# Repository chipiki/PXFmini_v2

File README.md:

# PXFmini_v2
It's attempt to make a second version of died project PXFmini

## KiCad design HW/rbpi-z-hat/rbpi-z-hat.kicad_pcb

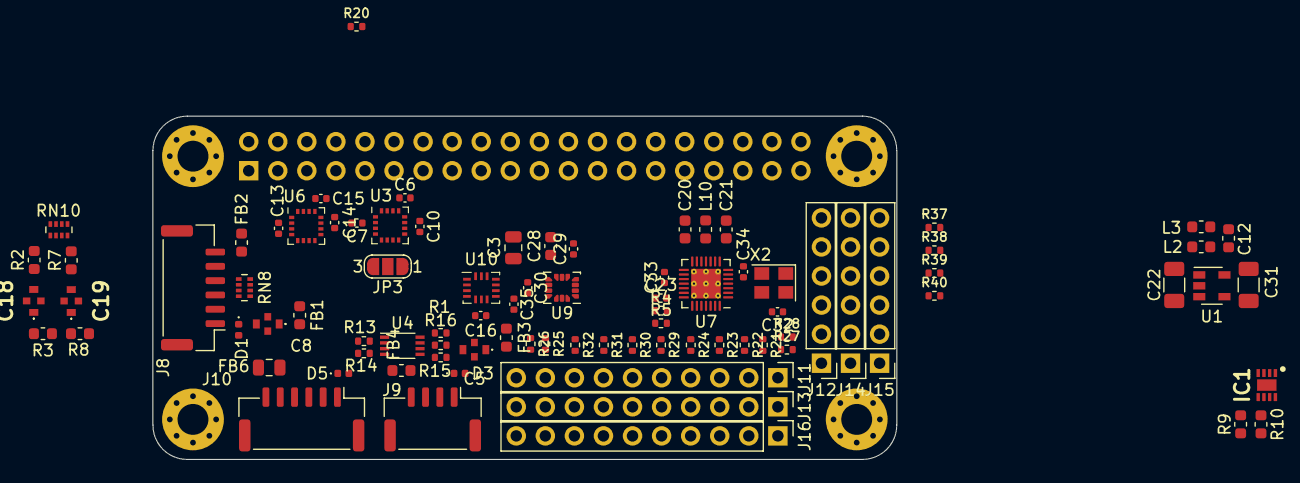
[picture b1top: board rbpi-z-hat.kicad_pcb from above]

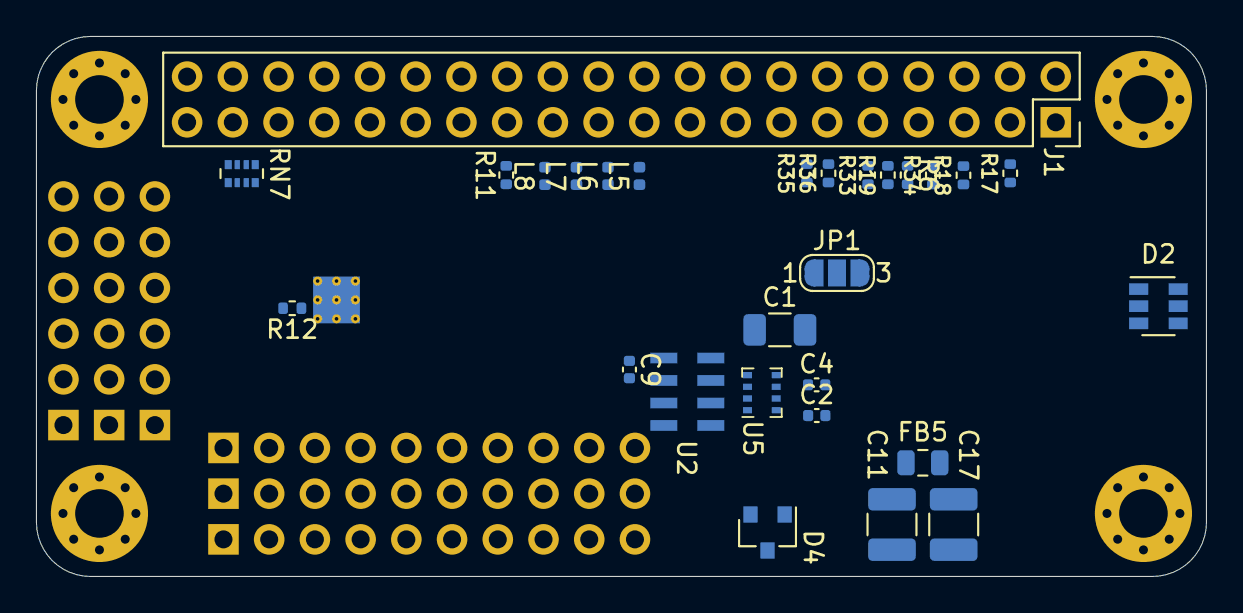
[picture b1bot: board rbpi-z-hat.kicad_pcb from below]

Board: 4 copper layers, 65.0 x 30.0 mm, 119 parts (28 on the bottom side), 92 nets, no tracks yet.

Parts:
C1, C22, C31: 22uF/10V; C_1206_3216Metric
C2, C4, C9: 100nF; C_0402_1005Metric
C3: 22uF/10V; C_0805_2012Metric
C5, C8: 1uF/16V/0805/NFM21PC105B1C3D; NFM21PC105B1C3D
C6, C7, C13, C15, C16, C23, C30, C32, C33, C34, C35: 0.1uF; C_0402_1005Metric
C10, C14: 4.7uF; C_0402_1005Metric
C11, C17: 22uF/16V; C_1210_3225Metric
C12: 100nF; C_0603_1608Metric
C18, C19: 1uF/16V/NFM21PC105B1C3D; NFM21PC105B1C3D
C20, C21: 10uF; C_0603_1608Metric
C28: 4.7uF; C_0603_1608Metric
C29: 10nF; C_0402_1005Metric
D1, D3, D5: PESD0402-140; D_0402_1005Metric
D2: ESDA5V3SC5; SOT-23-6
D4: PESD3V3S2UT; SOT-23
FB1, FB2, FB3, FB4: Ferrite_Bead; L_0603_1608Metric
FB5, FB6: MPZ2012S221AT000; L_0805_2012Metric
IC1: BQ24315DSGR; SON50P200X200X80-9N
J1: RBPI_CONN; PinSocket_2x20_P2.54mm_Vertical
J8: Conn_01x06_MountingPin; JST_GH_BM06B-GHS-TBT_1x06-1MP_P1.25mm_Vertical
J9: JST_GH; JST_GH_BM04B-GHS-TBT_1x04-1MP_P1.25mm_Vertical
J10: JST_GH; JST_GH_BM06B-GHS-TBT_1x06-1MP_P1.25mm_Vertical
J11, J13, J16: Conn_01x10; PinHeader_1x10_P2.54mm_Vertical
J12, J14, J15: Conn_01x06; PinHeader_1x06_P2.54mm_Vertical
JP1, JP3: SolderJumper_3_Open; SolderJumper-3_P1.3mm_Open_RoundedPad1.0x1.5mm_NumberLabels
L2, L3, L10: Ferrite_Bead; L_0603_1608Metric
L5, L6, L7, L8: Ferrite_Bead; L_0402_1005Metric
MH1, MH2, MH3, MH4: M2.5; MountingHole_2.7mm_M2.5_Pad_Via
R1: 200K; R_0402_1005Metric
R2, R7: 10K/0.1%; L_0603_1608Metric
R3, R8: 1M; L_0603_1608Metric
R4, R11, R12, R17, R18, R19, R20, R33, R34, R35, R36: 10K; R_0402_1005Metric
R5: 500K; R_0402_1005Metric
R6: 47K; R_0402_1005Metric
R9: 10K; R_0603_1608Metric
R10: 25K; R_0603_1608Metric
R13, R14, R15, R16: 1K5; R_0402_1005Metric
R21, R22, R23, R24, R25, R26, R27, R28, R29, R30, R31, R32, R37, R38, R39, R40: 220К; R_0402_1005Metric
RN7: 10K/4x0402; R_Array_Convex_4x0402
RN8: 120R; R_Array_Concave_4x0402
RN10: 10K/1%; R_Array_Concave_4x0402
U1: MIC5504-3.3YM5; SOT-23-5
U2: MS5611
U3: IST8310; LGA-16_3x3mm_P0.5mm
U4: PCA9306DC; VSSOP-8_2.3x2mm_P0.5mm
U5: BMP280; Bosch_LGA-8_2x2.5mm_P0.65mm_ClockwisePinNumbering
U6: MMC5883MA; LGA-16_3x3mm_P0.5mm
U7: STM32F031G6Ux; QFN-28-1EP_4x4mm_P0.4mm_EP2.6x2.6mm_ThermalVias
U9: ICM-42688-P; LGA-14_3x2.5mm_P0.5mm_LayoutBorder3x4y
U10: BMI160; Bosch_LGA-14_3x2.5mm_P0.5mm
X2: ASEMB-25.000MHZ-LC-T; Oscillator_SMD_Abracon_ASE-4Pin_3.2x2.5mm

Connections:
+3V3: C20.1, J1.1, J1.17, L10.1, R1.2, R11.1, R13.1, R14.1, R15.1, R16.1, R17.1, R18.1, R20.1, R33.1, R34.1, R35.1, R36.1, RN7.5 (R4.2), RN7.6 (R3.2), RN7.7 (R2.2), RN7.8 (R1.2), U4.1 (VREF1)
+5V: FB1.2, FB3.2, J1.2, J1.4
/BMI_nCS: J1.24, RN7.4 (R4.1), U10.12 (CSB)
/BMP_nCS: J1.26, R11.2, U5.2 (CSB)
/BQ24313/BQ_IN: C17.1, FB5.1, IC1.1 (IN)
/BQ24313/BQ_nCE: IC1.5 (~CE), R9.1
/BQ24313_OUT: C12.1, IC1.8 (OUT), L2.1
/CH32V203G6U6/CH32_EXTCLK: U7.2 (PF0), X2.3 (OUT)
/CH32V203G6U6/CH32_VDD: C21.1, C32.1, C33.1, C34.1, L10.2, R4.2, U7.5 (VDDA), U7.17 (VDD), X2.4 (Vdd)
/CH32V203G6U6/CH32_nRST: C23.1, R4.1, U7.4 (NRST)
/CH32V203G6U6/PWM_0: J11.1, R21.2
/CH32V203G6U6/PWM_1: J11.2, R22.2
/CH32V203G6U6/PWM_2: J11.3, R23.2
/CH32V203G6U6/PWM_3: J11.4, R24.2
/CH32V203G6U6/PWM_4: J11.5, R29.2
/CH32V203G6U6/PWM_5: J11.6, R30.2
/CH32V203G6U6/PWM_6: J11.7, R31.2
/CH32V203G6U6/PWM_7: J11.8, R32.2
/CH32V203G6U6/PWM_8: J11.9, R25.2
/CH32V203G6U6/PWM_9: J11.10, R26.2
/CH32V203G6U6/PWM_10: J12.1, R27.2
/CH32V203G6U6/PWM_11: J12.2, R28.2
/CH32V203G6U6/PWM_12: J12.3, R37.2
/CH32V203G6U6/PWM_13: J12.4, R38.2
/CH32V203G6U6/PWM_14: J12.5, R39.2
/CH32V203G6U6/PWM_15: J12.6, R40.2
/CH32V203G6U6/PWM_OUT0: R21.1, U7.14 (PB0)
/CH32V203G6U6/PWM_OUT1: R22.1, U7.15 (PB1)
/CH32V203G6U6/PWM_OUT2: R23.1, U7.24 (PB3)
/CH32V203G6U6/PWM_OUT3: R24.1, U7.25 (PB4)
/CH32V203G6U6/PWM_OUT4: R29.1, U7.26 (PB5)
/CH32V203G6U6/PWM_OUT5: R30.1, U7.9 (PA3)
/CH32V203G6U6/PWM_OUT6: R31.1, U7.10 (PA4)
/CH32V203G6U6/PWM_OUT7: R32.1, U7.11 (PA5)
/CH32V203G6U6/PWM_OUT8: R25.1, U7.12 (PA6)
/CH32V203G6U6/PWM_OUT9: R26.1, U7.13 (PA7)
/CH32V203G6U6/PWM_OUT10: R27.1, U7.18 (PA8)
/CH32V203G6U6/PWM_OUT11: R28.1, U7.19 (PA9)
/CH32V203G6U6/PWM_OUT12: R37.1, U7.20 (PA10)
/CH32V203G6U6/PWM_OUT13: R38.1, U7.21 (PA13)
/CH32V203G6U6/PWM_OUT14: R39.1, U7.22 (PA14)
/CH32V203G6U6/PWM_OUT15: R40.1, U7.23 (PA15)
/CH32V203G6U6/SERVO_POWER: J13.1, J13.2, J13.3, J13.4, J13.5, J13.6, J13.7, J13.8, J13.9, J13.10, J14.1, J14.2, J14.3, J14.4, J14.5, J14.6
/CUR_SENS: RN10.5 (R4.2), RN10.8 (R1.2), U7.6 (PA0)
/MS_nCS: U2.4 (CSB), U2.5 (CSB)
/PCA_nOE: R12.2, U7.3 (PF1)
/POWER_CONN/BAT_CUR: C18.1, J10.3, R3.1
/POWER_CONN/BAT_VOLT: C19.1, J10.4, R8.1
/SCL1: J1.3, R13.2, R17.2, U3.1 (SCL), U4.2 (SCL1), U6.1 (SCL), U7.27 (PB6)
/SDA1: J1.5, R14.2, R18.2, U3.16 (SDA), U4.3 (SDA1), U6.16 (SDA), U7.28 (PB7)
/SENSORS_POWER/MIC5504/MIC_VIN: C22.1, L2.2, U1.1 (VIN)
/SENS_FGND: C1.2, C2.2, C3.2, C4.2, C6.2, C7.2, C9.2, C10.2, C14.2, C16.2, C22.2, C28.2, C29.2, C30.2, C31.2, C35.2, JP1.3 (B), JP3.3 (B), L3.2, U1.2 (GND), U2.2 (PS), U2.3 (GND), U3.9 (VSS), U3.11 (VSS), U5.1 (GND), U5.7 (GND), U6.9 (GND), U6.11 (GND), U9.6 (GND), U10.6 (GNDIO), U10.7 (GND)
/SENS_MISO: L6.1, U2.6 (SDO), U5.5 (SDO), U9.1 (AP_SDO), U10.1 (SDO)
/SENS_MOSI: L5.1, U2.7 (SDI/SDA), U5.3 (SDI), U9.14 (AP_SDI), U10.14 (SDx)
/SENS_SCK: L7.1, U2.8 (SCLK), U5.4 (SCK), U9.13 (AP_SCLK), U10.13 (SCx)
/SENS_VDD: C1.1, C2.1, C3.1, C4.1, C6.1, C7.1, C9.1, C13.1, C15.1, C16.1, C28.1, C29.1, C30.1, C31.1, C35.1, JP1.1 (A), JP3.1 (A), U1.5 (VOUT), U2.1 (VDD), U3.2 (AVDD), U3.7 (VPP), U3.13 (DVDD), U5.6 (VDDIO), U5.8 (VDD), U6.2 (VDD), U6.13 (VDDIO), U9.5 (VDDIO), U9.8 (VDD), U10.2 (ASDx), U10.3 (ASCx), U10.5 (VDDIO), U10.8 (VDD), U10.10 (OCSB)
/SPI0_MISO: J1.21, L6.2, RN7.2 (R2.1)
/SPI0_MOSI: J1.19, L5.2, RN7.1 (R1.1)
/SPI0_SCK: J1.23, L7.2, RN7.3 (R3.1)
/UART_CTS: J1.12, R35.2, RN8.3 (R3.1)
/UART_RTS: J1.11, R36.2, RN8.4 (R4.1)
/UART_RX: J1.10, R33.2, RN8.2 (R2.1)
/UART_TX: J1.8, R34.2, RN8.1 (R1.1)
/VOLT_SENS: RN10.6 (R3.2), RN10.7 (R2.2), U7.7 (PA1)
/rbpi/Pin_7_PPM_SBUS_INPUT: J1.7, R6.1, R19.2
GNDD: C5.2, C8.2, C11.2, C12.2, C17.2, C18.2, C19.2, C20.2, C21.2, C23.2, C32.2, C33.2, C34.2, D1.2 (A2), D2.2 (COM), D2.5 (COM), D3.2 (A2), D4.3 (A), D5.2 (A2), FB2.1, FB4.1, FB6.1, IC1.2 (VSS), IC1.6 (VBAT), IC1.9 (EP), J1.6, J1.9, J1.14, J1.20, J1.25, J1.30, J1.34, J1.39, J8.MP (MountPin), J9.MP (MountPin), J10.MP (MountPin), J15.1, J15.2, J15.3, J15.4, J15.5, J15.6, J16.1, J16.2, J16.3, J16.4, J16.5, J16.6, J16.7, J16.8, J16.9, J16.10, L3.1, MH1.1, MH2.1, MH3.1, MH4.1, R3.2, R5.1, R6.2, R8.2, R9.2, R10.2, RN10.3 (R3.1), RN10.4 (R4.1), U4.4 (GND), U7.16 (VSS), X2.2 (GND)
unnamed: C5.1, FB3.1
unnamed: C8.1, FB1.1
unnamed: C13.2, C15.2
unnamed: C18.3, R2.1
unnamed: C19.3, R7.1
unnamed: C8.3, D1.1 (A1), J8.1
unnamed: D2.1 (TVS1), J8.5, RN8.5 (R4.2)
unnamed: D2.3 (TVS2), J8.4, RN8.6 (R3.2)
unnamed: D2.4 (TVS3), J8.3, RN8.7 (R2.2)
unnamed: D2.6 (TVS4), J8.2, RN8.8 (R1.2)
unnamed: C5.3, D3.1 (A1), J9.1
unnamed: C11.1, D5.1 (A1), FB5.2, J10.1, J10.2
unnamed: IC1.7 (ILIM), R10.1
unnamed: FB2.2, J8.6
unnamed: D4.2 (K), J9.2, R16.2, U4.6 (SCL2)
unnamed: D4.1 (K), J9.3, R15.2, U4.5 (SDA2)
unnamed: FB4.2, J9.4
unnamed: FB6.2, J10.5, J10.6
unnamed: JP1.2 (C), U3.6 (CAD1)
unnamed: JP3.2 (C), U3.5 (CAD0)
unnamed: R2.2, RN10.1 (R1.1)
unnamed: R7.2, RN10.2 (R2.1)
unnamed: C10.1, U3.10 (C1)
unnamed: R1.1, U4.7 (VREF2), U4.8 (EN)
unnamed: C14.1, U6.10 (CAP)
unnamed: R5.2, U7.1 (BOOT0)

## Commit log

2020-06-08 Commit...
2020-06-09 Commit..
2020-06-13 Removed MPU-9250
2020-08-11 Some changes in Sch & PCB
2021-08-04 feat[libs]: Added BMP388 symbol and footprint
2021-08-04 Changes in Sch
2021-08-04 Changes in Schematics
2021-08-06 Updated PCA9685.sch
2023-05-12 Some new things...
2023-05-12 PCA and ADC replaced by CH32V203G6U6
2023-05-15 Some update...
2024-01-18 Added schematics for IST8310
2024-01-18 Added schematics for QMC5883L
2024-01-19 Apdated Sch and PCB
2024-01-22 Replaced LSM9DS1 with BMI160/QMI8658C
2024-01-22 Changed capasitors to 0402
2024-01-22 Changes in PCB
2024-01-22 Changes in Sch & PCB
2024-01-23 Updated CH32V203G6U6.kicad_sch
2024-01-23 Removed unused files
2024-02-16 Changed some footprints
